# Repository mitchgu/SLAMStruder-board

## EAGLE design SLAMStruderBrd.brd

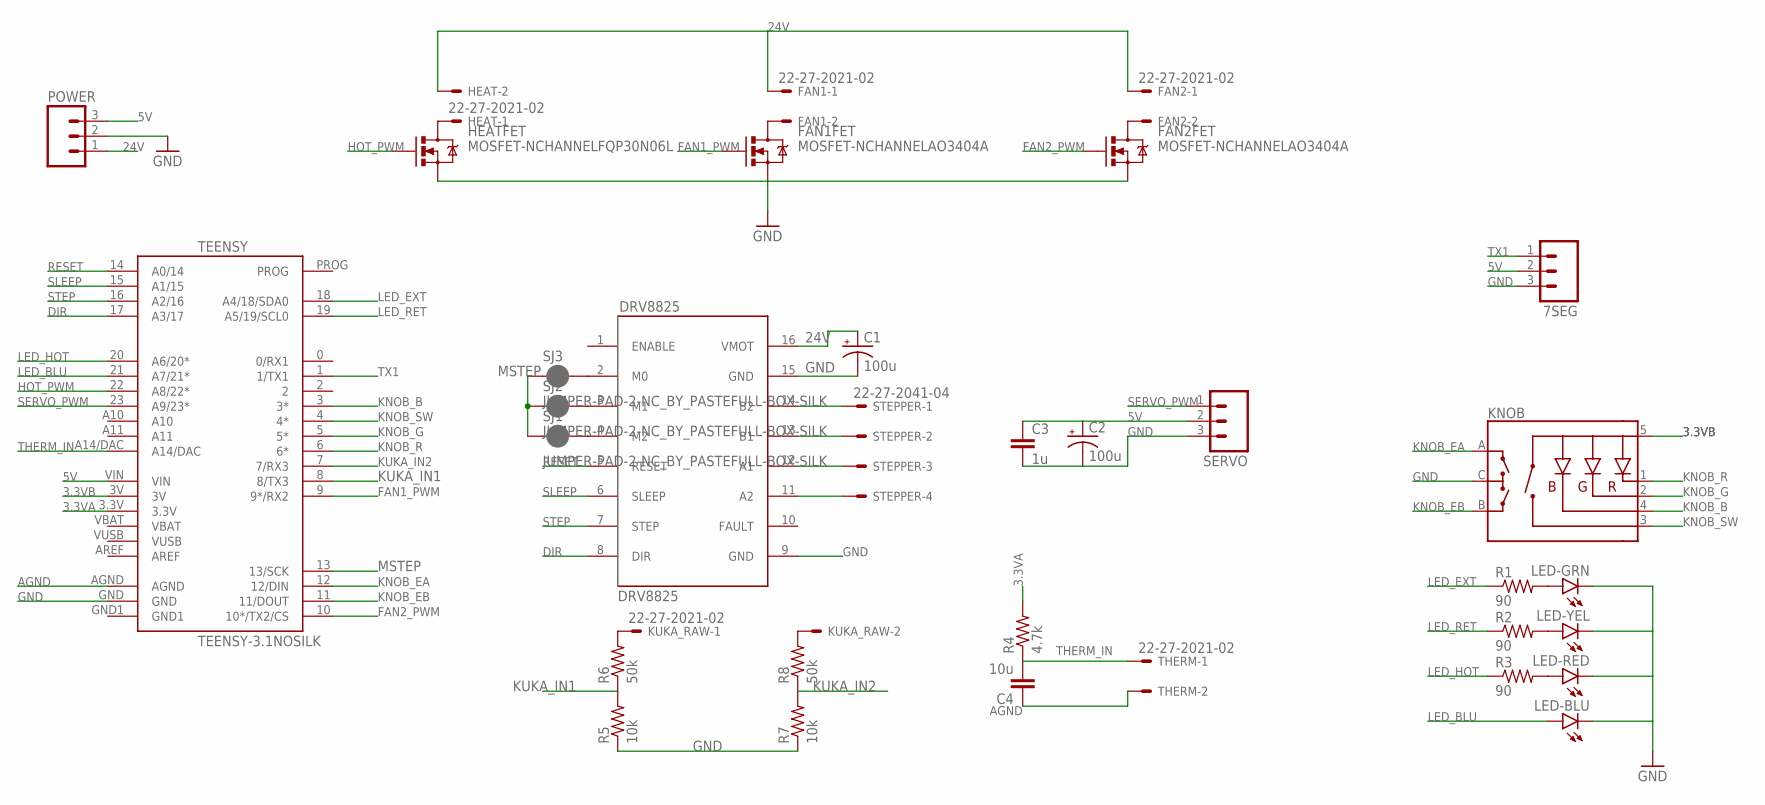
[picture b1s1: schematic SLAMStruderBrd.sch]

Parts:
7SEG: M031X03_NO_SILK; 1X03_NO_SILK
C1, C2: 100u; PANASONIC_E
C3: 1u; 0805
C4: 10u; 0805
DRV8825: DRV8825; STEPPER_DRIVER
FAN1, FAN2: 22-27-2021-02; 6410-02
FAN1FET, FAN2FET: MOSFET-NCHANNELAO3404A; SOT23-3
HEAT: 22-27-2021-02; 6410-02
HEATFET: MOSFET-NCHANNELFQP30N06L; TO220V
KNOB: ENCODER_RGB_CA; ENCODER_LED_3
KUKA_RAW: 22-27-2021-02; 6410-02
LED-BLU: LED5MM
LED-GRN: LED5MM
LED-RED: LED5MM
LED-YEL: LED5MM
POWER: M03SCREW; SCREWTERMINAL-3.5MM-3
R1, R2, R3: 90; 0805
R4: 4.7k; 0805
R5, R7: 10k; 0805
R6, R8: 50k; 0805
SERVO: M03PTH; 1X03
SJ1, SJ2, SJ3: JUMPER-PAD-2-NC_BY_PASTEFULL-BOX-SILK; PAD-JUMPER-2-NC_BY_PASTE_YES_SILK_FULL_BOX
STEPPER: 22-27-2041-04; 6410-04
TEENSY: TEENSY-3.1NOSILK; TEENSY-3.1_NOSILK
THERM: 22-27-2021-02; 6410-02

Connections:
3.3VA: R4.2, TEENSY.3.3V
3.3VB: KNOB.5 (+), TEENSY.3V
5V: 7SEG.2, C2.+, C3.1, POWER.3, SERVO.2, TEENSY.VIN
24V: C1.+, DRV8825.16 (VMOT), FAN1.1, FAN2.1, HEAT.2, POWER.1
AGND: C4.1, TEENSY.AGND, THERM.2
DIR: DRV8825.8 (DIR), TEENSY.17 (A3/17)
FAN1_PWM: FAN1FET.1 (G), TEENSY.9 (9*/RX2)
FAN2_PWM: FAN2FET.1 (G), TEENSY.10 (10*/TX2/CS)
GND: 7SEG.3, C1.-, C2.-, C3.2, DRV8825.9 (GND), DRV8825.15 (GND), FAN1FET.2 (S), FAN2FET.2 (S), HEATFET.3 (S), KNOB.C, LED-BLU.K (C), LED-GRN.K (C), LED-RED.K (C), LED-YEL.K (C), POWER.2, R5.1, R7.1, SERVO.3, TEENSY.GND
HOT_PWM: HEATFET.1 (G), TEENSY.22 (A8/22*)
KNOB_B: KNOB.4 (-B), TEENSY.3 (3*)
KNOB_EA: KNOB.A, TEENSY.12 (12/DIN)
KNOB_EB: KNOB.B, TEENSY.11 (11/DOUT)
KNOB_G: KNOB.2 (-G), TEENSY.5 (5*)
KNOB_R: KNOB.1 (-R), TEENSY.6 (6*)
KNOB_SW: KNOB.3 (SW), TEENSY.4 (4*)
KUKA_IN1: R5.2, R6.1, TEENSY.8 (8/TX3)
KUKA_IN2: R7.2, R8.1, TEENSY.7 (7/RX3)
LED_BLU: LED-BLU.A, TEENSY.21 (A7/21*)
LED_EXT: R1.1, TEENSY.18 (A4/18/SDA0)
LED_HOT: R3.1, TEENSY.20 (A6/20*)
LED_RET: R2.1, TEENSY.19 (A5/19/SCL0)
MSTEP: SJ1.1, SJ2.1, SJ3.1, TEENSY.13 (13/SCK)
unnamed: DRV8825.14 (B2), STEPPER.1
unnamed: DRV8825.13 (B1), STEPPER.2
unnamed: HEAT.1, HEATFET.2 (D)
unnamed: DRV8825.11 (A2), STEPPER.4
unnamed: DRV8825.12 (A1), STEPPER.3
unnamed: FAN1.2, FAN1FET.3 (D)
unnamed: FAN2.2, FAN2FET.3 (D)
unnamed: LED-GRN.A, R1.2
unnamed: LED-YEL.A, R2.2
unnamed: LED-RED.A, R3.2
unnamed: DRV8825.4 (M2), SJ1.2
unnamed: DRV8825.3 (M1), SJ2.2
unnamed: DRV8825.2 (M0), SJ3.2
unnamed: KUKA_RAW.1, R6.2
unnamed: KUKA_RAW.2, R8.2
RESET: DRV8825.5 (RESET), TEENSY.14 (A0/14)
SERVO_PWM: SERVO.1, TEENSY.23 (A9/23*)
SLEEP: DRV8825.6 (SLEEP), TEENSY.15 (A1/15)
STEP: DRV8825.7 (STEP), TEENSY.16 (A2/16)
THERM_IN: C4.2, R4.1, TEENSY.A14/DAC, THERM.1
TX1: 7SEG.1, TEENSY.1 (1/TX1)

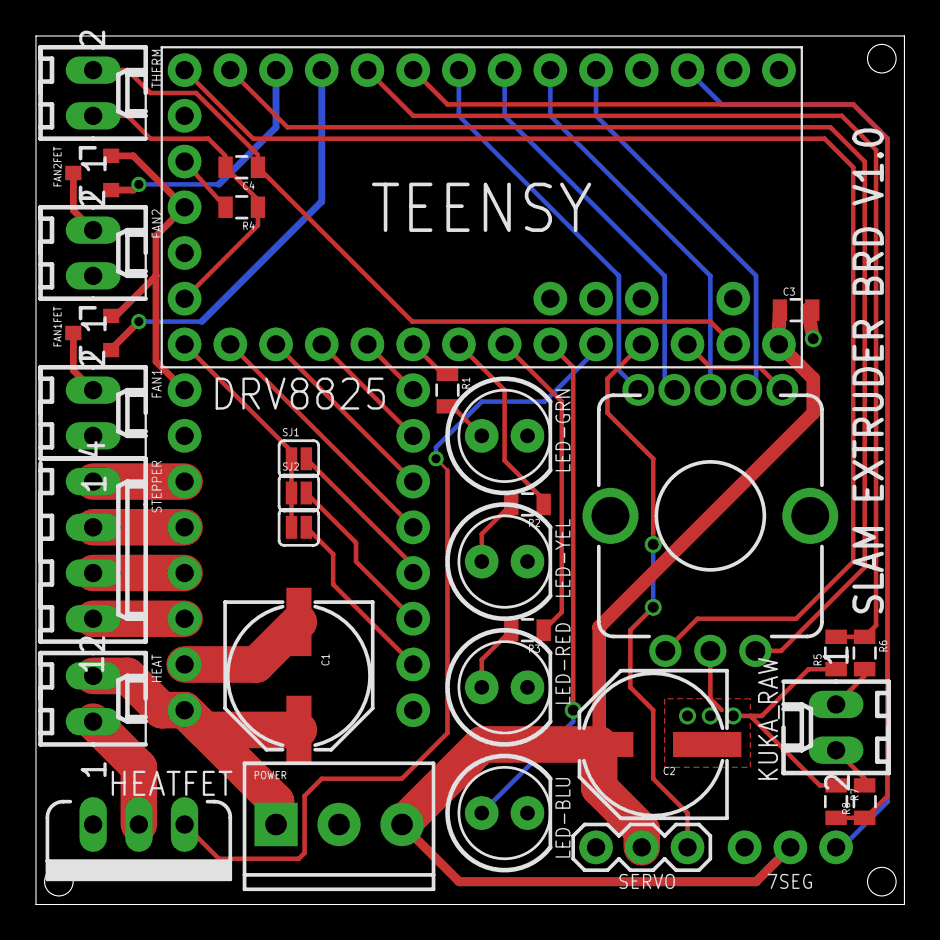
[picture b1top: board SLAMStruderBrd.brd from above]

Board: 2 copper layers, 48.2 x 48.2 mm, 34 parts (0 on the bottom side), 44 nets.

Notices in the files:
parts and their libraries:
SparkFun-Boards: Licensing: Creative Commons ShareAlike 4.0 International - https://creativecommons.org/licenses/by-sa/4.0
